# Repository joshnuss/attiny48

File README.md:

# ATTINY48/88 Dev Board

Development breakout board for Atmel ATTINY48/88.

Built with [KiCAD](http://kicad-pcb.org/).

## License

MIT

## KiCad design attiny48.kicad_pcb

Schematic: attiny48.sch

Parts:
C1: 100u; C_0805_2012Metric_Pad1.15x1.40mm_HandSolder
D1: LED; D_0805_2012Metric_Pad1.15x1.40mm_HandSolder
J1: POWER; PinSocket_1x02_P1.00mm_Vertical
J2: PORTA; PinHeader_1x04_P1.00mm_Vertical
J3: PORTB; PinHeader_1x08_P1.00mm_Vertical
J4: PORTC; PinHeader_1x08_P1.00mm_Vertical
J5: PORTD; PinHeader_1x08_P1.00mm_Vertical
J6: ICSP; PinHeader_2x03_P1.00mm_Vertical
R1, R2: R; R_0805_2012Metric_Pad1.15x1.40mm_HandSolder
U1: ATtiny88-AU; TQFP-32_7x7mm_P0.8mm

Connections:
+3V3: C1.1, J1.1, R1.2, R2.1, U1.4 (VCC), U1.18 (AVCC); also elsewhere on the board
GND: C1.2, D1.1, J1.2, U1.5 (GND), U1.21 (GND); also elsewhere on the board
MISO: J3.5, U1.16 (PB4); also elsewhere on the board
MOSI: J3.4, U1.15 (PB3); also elsewhere on the board
unnamed: D1.2, R1.1
unnamed: J2.1, U1.19 (PA0)
unnamed: J2.2, U1.22 (PA1)
unnamed: J2.3, U1.3 (PA2)
unnamed: J2.4, U1.6 (PA3)
unnamed: J3.1, U1.12 (PB0)
unnamed: J3.2, U1.13 (PB1)
unnamed: J3.3, U1.14 (PB2)
unnamed: J3.7, U1.7 (PB6)
unnamed: J3.8, U1.8 (PB7)
unnamed: J4.1, U1.23 (PC0)
unnamed: J4.2, U1.24 (PC1)
unnamed: J4.3, U1.25 (PC2)
unnamed: J4.4, U1.26 (PC3)
unnamed: J4.5, U1.27 (PC4)
unnamed: J4.6, U1.28 (PC5)
unnamed: J4.8, U1.20 (PC7)
unnamed: J5.1, U1.30 (PD0)
unnamed: J5.2, U1.31 (PD1)
unnamed: J5.3, U1.32 (PD2)
unnamed: J5.4, U1.1 (PD3)
unnamed: J5.5, U1.2 (PD4)
unnamed: J5.6, U1.9 (PD5)
unnamed: J5.7, U1.10 (PD6)
unnamed: J5.8, U1.11 (PD7)
RST: J4.7, R2.2, U1.29 (~RESET~/PC6); also elsewhere on the board
SCK: J3.6, U1.17 (PB5); also elsewhere on the board

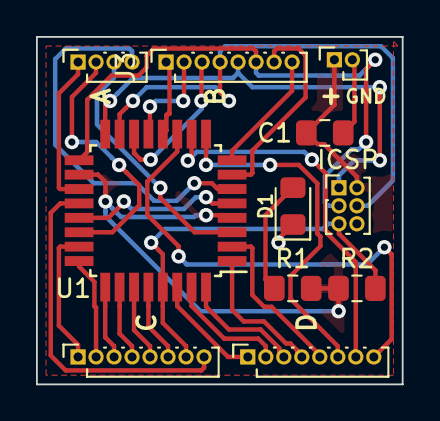
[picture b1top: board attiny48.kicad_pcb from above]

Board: 2 copper layers, 20.3 x 19.3 mm, 11 parts (0 on the bottom side), 31 nets.

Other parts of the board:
ICSP: ICSP; PinHeader_2x03_P1.00mm_Vertical

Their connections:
+3V3: ICSP.2; also elsewhere on the board
GND: ICSP.6; also elsewhere on the board
MISO: ICSP.1; also elsewhere on the board
MOSI: ICSP.4; also elsewhere on the board
RST: ICSP.5; also elsewhere on the board
SCK: ICSP.3; also elsewhere on the board

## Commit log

2018-10-16 Adds symbols to PCB
2018-10-16 Adds 3d models of board
2018-10-16 Adds datasheet for ATTINY
2018-10-16 Adds Readme
2018-10-16 Add model to readme
